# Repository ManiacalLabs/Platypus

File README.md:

# Platypus CNC / Laser Control Board

The Platypus is an Open Hardware CNC / Laser control board for running 2-axis GRBL with a wide variety of stepper motor driver options.

Unlike other Grbl boards that are just Arduino shields, the Platypus is a fully integrated solution with a built-in ATMega328p microcontroller and USB UART. 

Also, while other Grbl boards ignore it, the Platypus natively supports configuring Trinamic (TMC) StepStick drivers like the TMC2100 and TMC2208. Unlike normal StepStick motor drivers, the TMC variants use tri-state config pins which the Platypus provides.

# Specs

- Integrated ATMega328p Microcontroller (no arduino needed)
- CH340 USB to UART converter
- Screw terminals for all connections (plus male headers for motor and laser)
- Supports all standard StepStick-style motor drivers including TMC2100 and TMC2208
- Only 57mm x 75mm
- Robust USB-B connector

# Important Links

- [Usage](docs/Usage.md)
- [Assembly](docs/Assembly.md)

# Dimensions

# Contributing

This repository makes use of `git` submodules (primarily to handle KiCAD symbol and footprint libraries) and must be cloned with extra options.

Either clone the repo via:

```
git clone --recurse-submodules git@github.com:ManiacalLabs/Platypus.git
```

Or, if you already have the repo cloned or are using a fork:

```
git clone <EngravinatorRepo>
cd Engravinator
git submodule init
git submodule update
```

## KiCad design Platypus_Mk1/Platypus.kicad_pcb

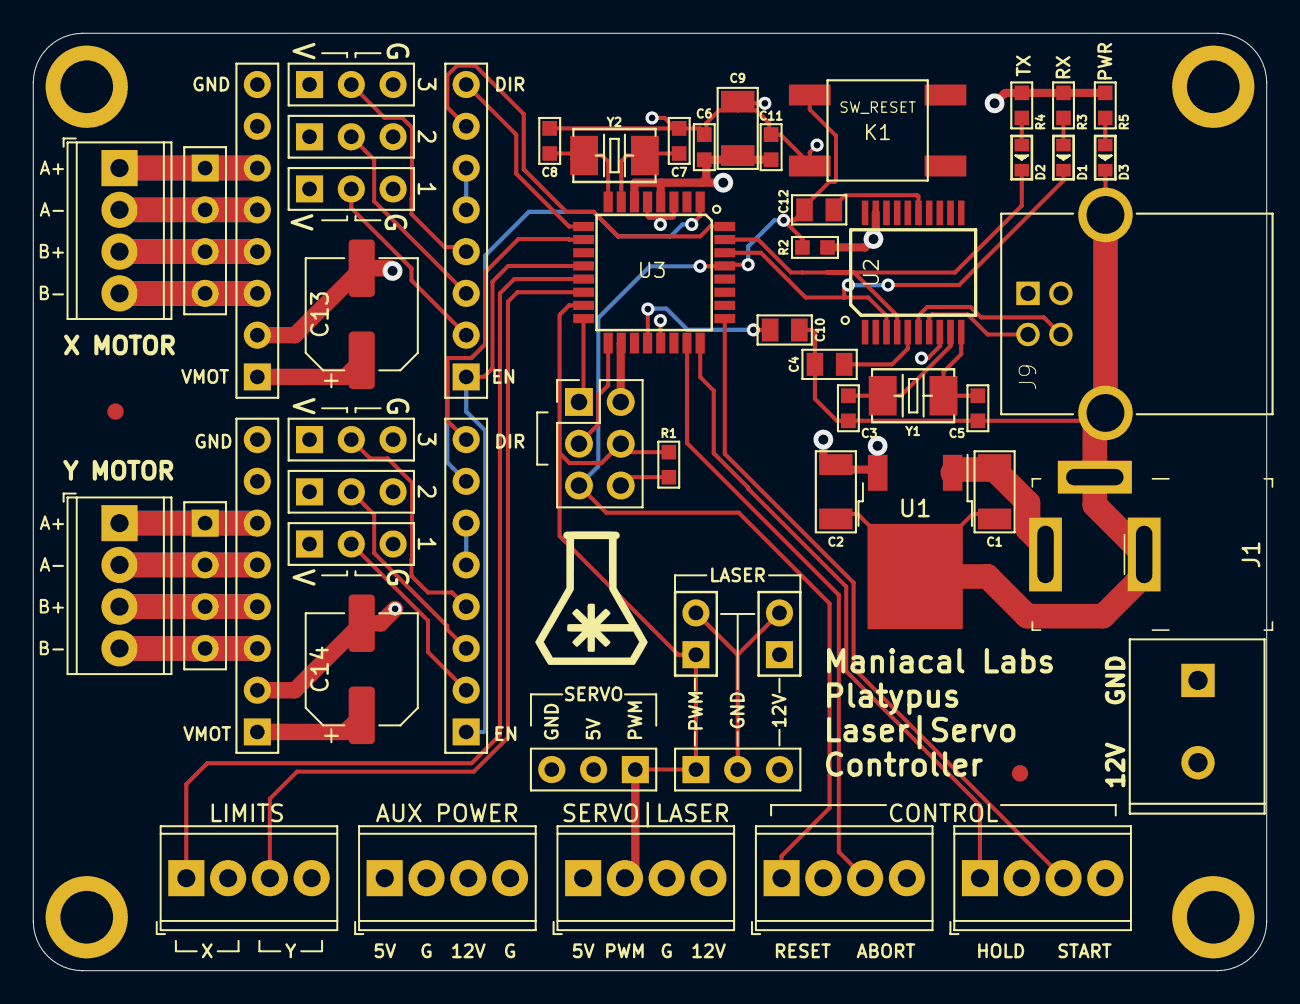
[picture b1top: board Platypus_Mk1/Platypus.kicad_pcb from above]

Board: 4 copper layers, 75.0 x 57.0 mm, 61 parts (0 on the bottom side), 47 nets.

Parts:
C1, C2, C9: 10uF; C1206
C3, C5, C7, C8: 22pF; C0603
C4, C10, C12: 100nF; C0805
C6, C11: 1uF; C0603
C13, C14: 47uF; CP_Elec_6.3x5.4
CN1: SERVO_PWM; H3-2.54
CN2, CN3, CN4, CN7, CN8, CN9: CFG1; H3-2.54
CN5, CN10: FEMALE_LEFT; H8-2.54
CN6, CN11: FEMALE_RIGHT; H8-2.54
CN12: LASER_CONN; H3-2.54
D1, D2, D3: LED_RED; LED-0603
FID1, FID2: Fiducial; Fiducial_1mm_Dia_2mm_Outer
H1, H2, H3, H4: Mount; MountingHole_2.5mm_Pad
J1: PJ-202AH; Barrel_Jack_5.5mmODx2.1mmID_PJ-202A
J2: TermLaser; TerminalBlock_Phoenix_MPT-0,5-4-2.54_1x04_P2.54mm_Horizontal
J3: TermStop; TerminalBlock_Phoenix_MPT-0,5-4-2.54_1x04_P2.54mm_Horizontal
J4: LASER_PWR; H2-2.54
J5: LASER_PULSE; H2-2.54
J6: TermControl; TerminalBlock_Phoenix_MPT-0,5-4-2.54_1x04_P2.54mm_Horizontal
J7: TermLimit; TerminalBlock_Phoenix_MPT-0,5-4-2.54_1x04_P2.54mm_Horizontal
J8: TermAux; TerminalBlock_Phoenix_MPT-0,5-4-2.54_1x04_P2.54mm_Horizontal
J9: UJ2-BH-1-TH; CUI_UJ2-BH-1-TH
J10: ICSP; PinHeader_2x03_P2.54mm_Vertical
J11, J13: MotorTerm; TerminalBlock_Phoenix_MPT-0,5-4-2.54_1x04_P2.54mm_Horizontal
J12, J14: MotorHeader; H4-2.54
J15: 12V_TERM; H2-5.0-10.5X8.0MM
K1: SW_RESET; SW4-SMD-6.0X6.0X5.0MM
R1, R2: 10K; R0603
R3, R4, R5: 1K; R0603
U1: CJ7805; TO-252-2
U2: INTERFACE-CH340T_SSOP20_; SSOP20-0.65-7.6X5.2MM
U3: MCU-ATMEGA328P-AU_TQFP32_; TQFP32-0.8-7X7MM
Y1: 12MHz; X2-SMD-5.0X3.2X1.3MM
Y2: 16MHZ; X2-SMD-5.0X3.2X1.3MM

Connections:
5V: C2.1, C6.2, C9.1, C11.2, CN1.2, CN2.1, CN3.1, CN4.1, CN6.7, CN7.1, CN8.1, CN9.1, CN11.7, J2.1, J8.1, J10.2, R2.2, R3.2, R4.1, R5.2, U1.3, U2.19, U3.4, U3.6, U3.18
/Arduino Nano/D12: J10.1, U3.16
/Arduino Nano/D13: J10.3, U3.17
/GRBL_ABORT: J3.3, U3.23
/GRBL_RX: D1.2, U2.3, U3.30
/GRBL_TX: D2.2, U2.4, U3.31
/HOLD: J6.1, U3.24
/NANO_RESET: C12.1, J3.1, J10.5, K1.3, R2.1, U3.29
/PULSE: CN1.1, CN12.1, J2.2, J5.1, J10.4, R1.2, U3.15
/START: J6.3, U3.25
/STEP_EN: CN5.1, CN10.1, U3.12
/StepDriverX/CFG1: CN2.2, CN5.2
/StepDriverX/CFG2: CN3.2, CN5.3
/StepDriverX/CFG3: CN4.2, CN5.4
/StepDriverY/CFG1: CN7.2, CN10.2
/StepDriverY/CFG2: CN8.2, CN10.3
/StepDriverY/CFG3: CN9.2, CN10.4
/VIN_12V: C1.1, C13.1, C14.1, CN6.1, CN11.1, CN12.3, J1.1, J2.4, J4.1, J8.3, J15.2, U1.1
/X_DIR: CN5.8, U3.9
/X_LIMIT: J7.1, U3.13
/X_STEP: CN5.7, U3.32
/Y_DIR: CN10.8, U3.10
/Y_LIMIT: J7.3, U3.14
/Y_STEP: CN10.7, U3.1
GND: C1.2, C2.2, C3.1, C4.2, C5.1, C6.1, C7.2, C8.1, C9.2, C10.2, C11.1, C13.2, C14.2, CN1.3, CN2.3, CN3.3, CN4.3, CN6.2, CN6.8, CN7.3, CN8.3, CN9.3, CN11.2, CN11.8, CN12.2, D3.2, H1.1, H2.1, H3.1, H4.1, J1.2, J1.3, J2.3, J3.2, J3.4, J4.2, J5.2, J6.2, J6.4, J7.2, J7.4, J8.2, J8.4, J9.4, J9.SH1, J9.SH2, J10.6, J15.1, K1.4, R1.1, U1.2, U2.8, U3.3, U3.5, U3.21
unnamed: C3.2, U2.9, Y1.2
unnamed: C4.1, U2.5
unnamed: C5.2, U2.10, Y1.1
unnamed: C7.1, U3.7, Y2.1
unnamed: C8.2, U3.8, Y2.2
unnamed: C10.1, U3.20
unnamed: C12.2, U2.15
unnamed: CN5.5, CN5.6
unnamed: CN6.3, J11.4, J12.4
unnamed: CN6.4, J11.3, J12.3
unnamed: CN6.5, J11.2, J12.2
unnamed: CN6.6, J11.1, J12.1
unnamed: CN10.5, CN10.6
unnamed: CN11.3, J13.4, J14.4
unnamed: CN11.4, J13.3, J14.3
unnamed: CN11.5, J13.2, J14.2
unnamed: CN11.6, J13.1, J14.1
unnamed: D1.1, R3.1
unnamed: D2.1, R4.2
unnamed: D3.1, R5.1
unnamed: J9.2, U2.7
unnamed: J9.3, U2.6

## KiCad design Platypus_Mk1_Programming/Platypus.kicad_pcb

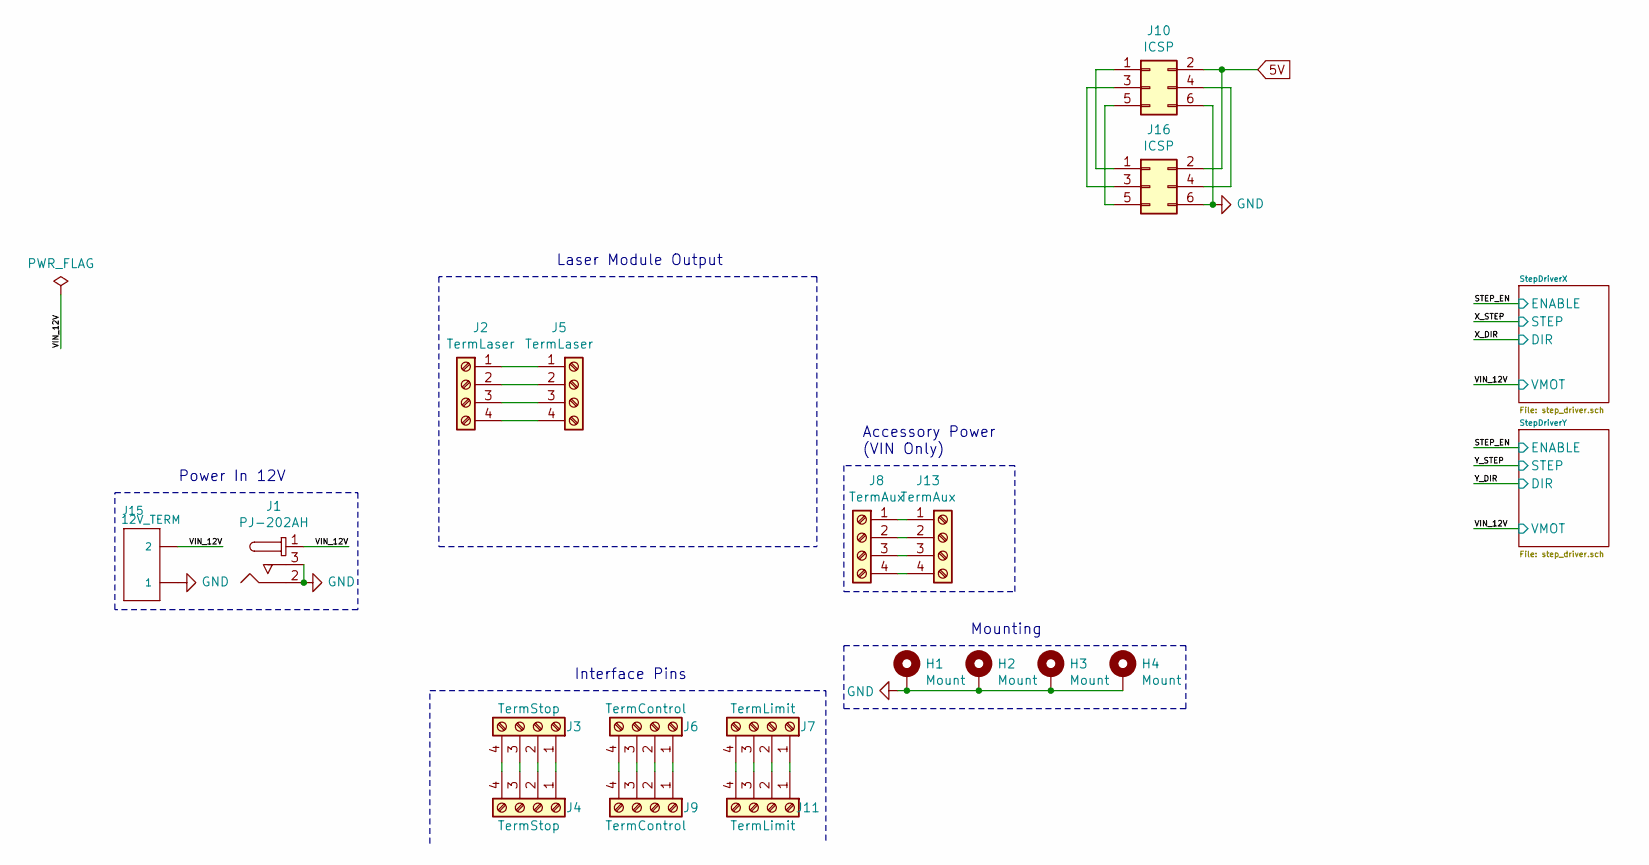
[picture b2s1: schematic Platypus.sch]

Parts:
H1, H2, H3, H4: Mount; MountingHole_2.5mm_Pad
J1: PJ-202AH; Barrel_Jack_5.5mmODx2.1mmID_PJ-202A; MPN PJ-202AH; Digi-Key_PN CP-202AH-ND
J2, J5: TermLaser; TerminalBlock_Phoenix_MPT-0,5-4-2.54_1x04_P2.54mm_Horizontal; MPN GS019-2.54-04P-5
J3, J4: TermStop; TerminalBlock_Phoenix_MPT-0,5-4-2.54_1x04_P2.54mm_Horizontal; MPN GS019-2.54-04P-5
J6, J9: TermControl; TerminalBlock_Phoenix_MPT-0,5-4-2.54_1x04_P2.54mm_Horizontal; MPN GS019-2.54-04P-5
J7, J11: TermLimit; TerminalBlock_Phoenix_MPT-0,5-4-2.54_1x04_P2.54mm_Horizontal; MPN GS019-2.54-04P-5
J8, J13: TermAux; TerminalBlock_Phoenix_MPT-0,5-4-2.54_1x04_P2.54mm_Horizontal; MPN GS019-2.54-04P-5
J10, J16: ICSP; PinHeader_2x03_P2.54mm_Vertical; MPN P125-12A1BS116A1
J15: 12V_TERM; H2-5.0-10.5X8.0MM

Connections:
5V: J10.2, J16.2; also elsewhere on the board
/VIN_12V: J1.1, J15.2; also elsewhere on the board
GND: H1.1, H2.1, H3.1, H4.1, J1.2, J1.3, J10.6, J15.1, J16.6; also elsewhere on the board
unnamed: J2.1, J5.1
unnamed: J2.2, J5.2
unnamed: J2.3, J5.3
unnamed: J2.4, J5.4
unnamed: J3.1, J4.1
unnamed: J3.2, J4.2
unnamed: J3.3, J4.3
unnamed: J3.4, J4.4
unnamed: J6.1, J9.1
unnamed: J6.2, J9.2
unnamed: J6.3, J9.3
unnamed: J6.4, J9.4
unnamed: J10.1, J16.1
unnamed: J10.3, J16.3
unnamed: J10.4, J16.4
unnamed: J10.5, J16.5
unnamed: J7.1, J11.1
unnamed: J7.2, J11.2
unnamed: J7.3, J11.3
unnamed: J7.4, J11.4
unnamed: J8.1, J13.1
unnamed: J8.2, J13.2
unnamed: J8.3, J13.3
unnamed: J8.4, J13.4

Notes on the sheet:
Accessory Power (VIN Only)
Laser Module Output
Interface Pins
Power In 12V
Mounting

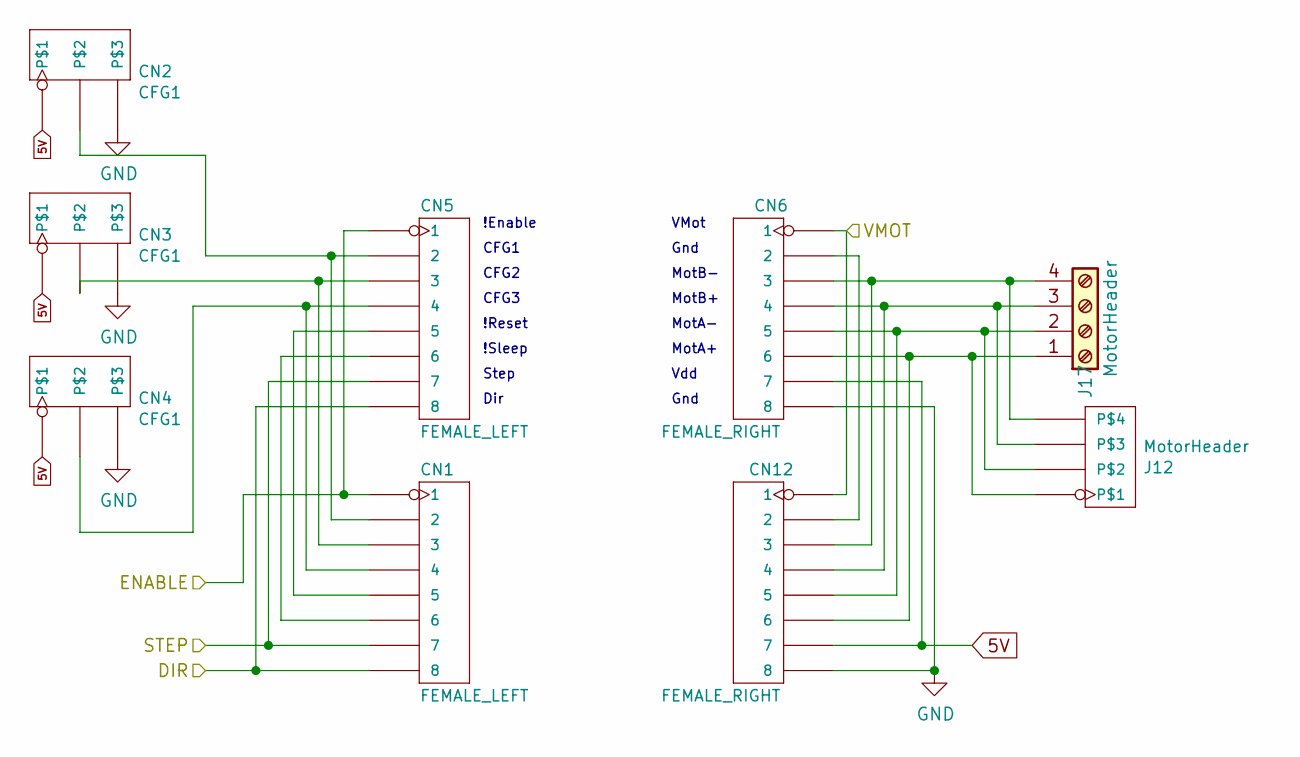
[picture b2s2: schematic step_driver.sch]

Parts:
CN1, CN5: FEMALE_LEFT; H8-2.54; MPN F185-1108A1BSYC1
CN2, CN3, CN4: CFG1; H3-2.54
CN6, CN12: FEMALE_RIGHT; H8-2.54; MPN F185-1108A1BSYC1
J12: MotorHeader; H4-2.54; MPN P125-1104A0BS116A1
J17: MotorHeader; TerminalBlock_Phoenix_MPT-0,5-4-2.54_1x04_P2.54mm_Horizontal; MPN GS019-2.54-04P-5

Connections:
5V: CN2.1, CN3.1, CN4.1, CN6.7, CN12.7; also elsewhere on the board
/STEP_EN: CN1.1, CN5.1; also elsewhere on the board
/VIN_12V: CN6.1, CN12.1; also elsewhere on the board
/X_DIR: CN1.8, CN5.8
/X_STEP: CN1.7, CN5.7
GND: CN2.3, CN3.3, CN4.3, CN6.8, CN12.8; also elsewhere on the board
unnamed: CN1.2, CN2.2, CN5.2
unnamed: CN1.3, CN3.2, CN5.3
unnamed: CN1.4, CN4.2, CN5.4
unnamed: CN1.5, CN5.5
unnamed: CN1.6, CN5.6
unnamed: CN6.2, CN12.2
unnamed: CN6.3, CN12.3, J12.4, J17.4
unnamed: CN6.4, CN12.4, J12.3, J17.3
unnamed: CN6.5, CN12.5, J12.2, J17.2
unnamed: CN6.6, CN12.6, J12.1, J17.1

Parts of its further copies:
CN7, CN8, CN9: CFG1; H3-2.54
CN10, CN13: FEMALE_LEFT; H8-2.54; MPN F185-1108A1BSYC1
CN11, CN14: FEMALE_RIGHT; H8-2.54; MPN F185-1108A1BSYC1
J14: MotorHeader; H4-2.54; MPN P125-1104A0BS116A1
J18: MotorHeader; TerminalBlock_Phoenix_MPT-0,5-4-2.54_1x04_P2.54mm_Horizontal; MPN GS019-2.54-04P-5

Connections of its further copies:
5V: CN7.1, CN8.1, CN9.1, CN11.7, CN14.7; also elsewhere on the board
/STEP_EN: CN10.1, CN13.1; also elsewhere on the board
/VIN_12V: CN11.1, CN14.1; also elsewhere on the board
/Y_DIR: CN10.8, CN13.8
/Y_STEP: CN10.7, CN13.7
GND: CN7.3, CN8.3, CN9.3, CN11.8, CN14.8; also elsewhere on the board
unnamed: CN7.2, CN10.2, CN13.2
unnamed: CN8.2, CN10.3, CN13.3
unnamed: CN9.2, CN10.4, CN13.4
unnamed: CN10.5, CN13.5
unnamed: CN10.6, CN13.6
unnamed: CN11.2, CN14.2
unnamed: CN11.3, CN14.3, J14.4, J18.4
unnamed: CN11.4, CN14.4, J14.3, J18.3
unnamed: CN11.5, CN14.5, J14.2, J18.2
unnamed: CN11.6, CN14.6, J14.1, J18.1

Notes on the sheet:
!Enable
CFG1
CFG2
CFG3
!Reset
!Sleep
Step
Dir
VMot
Gnd
MotB-
MotB+
MotA-
MotA+
Vdd

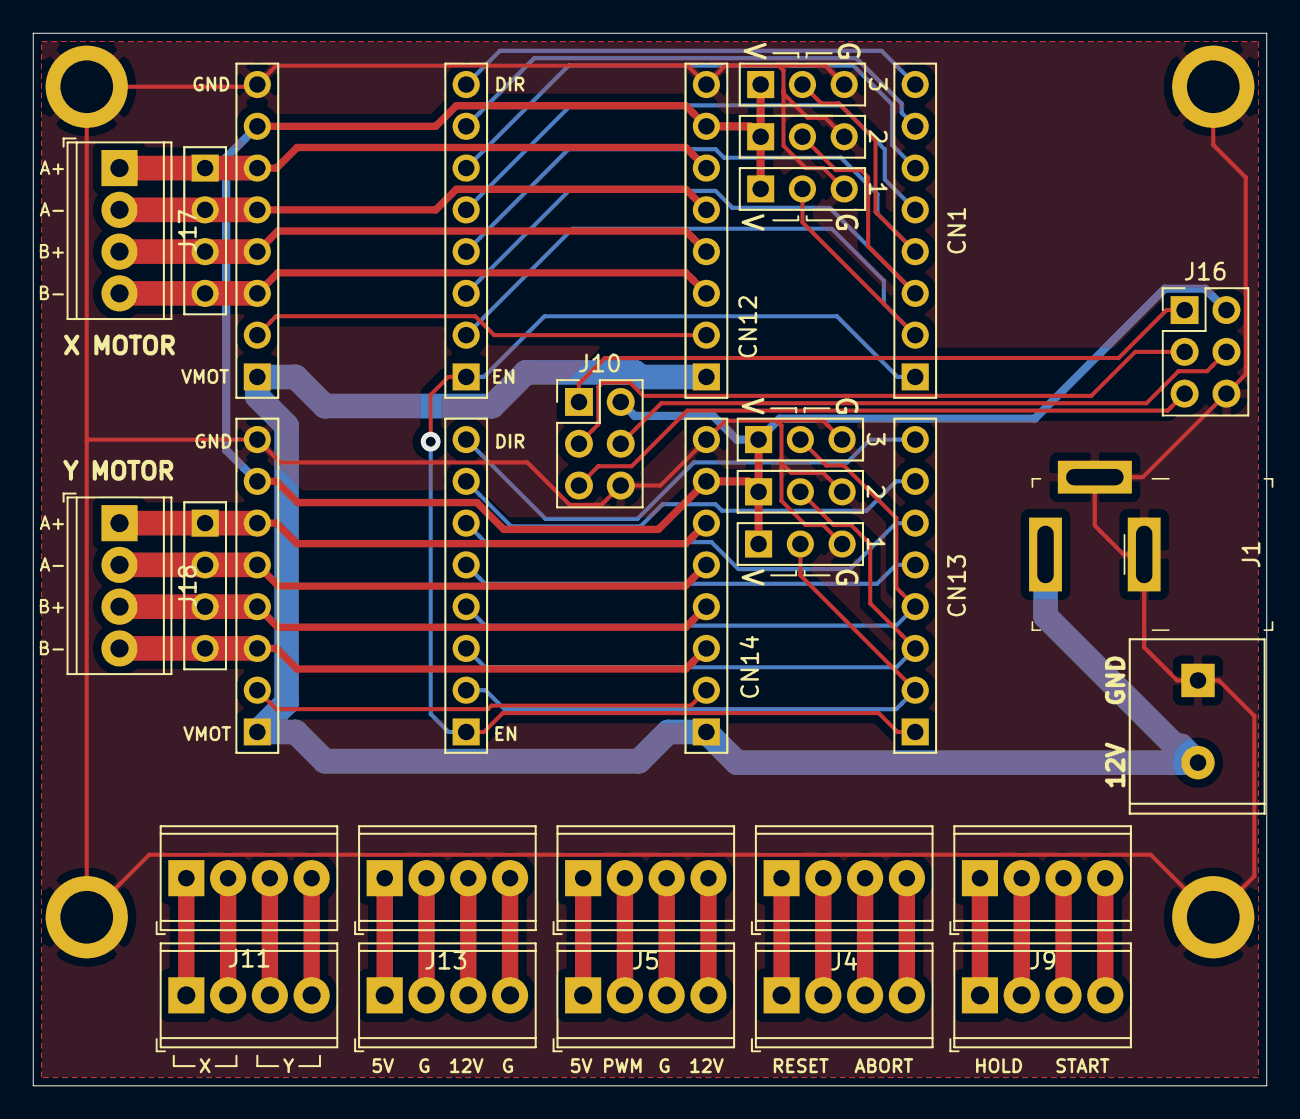
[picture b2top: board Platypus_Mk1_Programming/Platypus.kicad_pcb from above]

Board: 2 copper layers, 75.0 x 64.0 mm, 36 parts (0 on the bottom side), 52 nets.

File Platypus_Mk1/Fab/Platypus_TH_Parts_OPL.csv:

Part/Designator,Manufacture Part Number/Seeed SKU,Quantity
"J4,J5",320020016,2
"J12,J14",320020017,2
J10,320020077,1
"CN1,CN2,CN3,CN4,CN7,CN8,CN9,CN12",320020079,8
"CN5,CN6,CN10,CN11",320030061,4
J15,320110031,1
"J2,J3,J6,J7,J8,J11,J13",320110118 - GS019 4 pin screw terminal ,7

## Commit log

2019-08-06 initial setup
2019-08-06 Added Arduino Nano component
2019-08-06 Add nano to main sheet
2019-08-06 Starting on step driver module
2019-08-07 Minor update to stepper
2019-08-07 Almost complete schematic
2019-08-07 adding digikey libs
2019-08-07 Complete schematic
2019-08-07 Set more footprints
2019-08-07 Add IC footprints
2019-08-08 Creating Pi layout
2019-08-08 Probably giving up on Pi option
2019-08-09 More power routing
2019-08-09 power and nano cleanup
2019-08-09 temp remove submodules
2019-08-09 Add back submodules
2019-08-09 Added license and readme
2019-08-10 Mostly final layout
2019-08-10 Near complete layout
2019-08-10 Beta v1
2019-08-10 Starting to add 3D models
2019-08-10 Finished adding 3D models
2019-08-10 Fixing 10uF caps
2019-08-10 fix 2 missing cap models
2019-08-14 Add fab files
2019-08-29 Moving into own repo
2019-08-29 Update submodules
2019-08-29 Trying to fix submodules
2019-08-29 Readd submodules correctly
2019-08-29 Look, submodule is hard
2019-08-29 Fix README
2019-08-30 Increase mount hole size
2019-09-09 Change RX/TX LEDs. Add new laser conn
2019-09-09 rework for component moves
2019-09-10 Adding platypus graphic
2019-09-11 Update fab files
2019-09-11 Addinge license note to board back
2019-09-11 Adding stepper driver labels
2019-10-09 Adding step file and solder jig
2019-10-11 remove boarder from gerbers
2019-10-17 Add programming board
2019-11-05 Fixing programmer hole sizes
2019-11-10 Adding usage doc
2019-11-10 Add LightBurn setup
2019-11-11 add laserweb doc
2019-11-11 Added driver section
2019-11-11 Added specs
2019-11-19 Adding updated step file
2019-11-19 Add flash and test utils
2019-11-21 update base flash tools
2019-11-23 Adding movement checks
2019-12-15 Adding assembly guide
2019-12-15 Add assembly link
2019-12-15 Adding dimensions doc
2019-12-16 tweak description
2019-12-16 tweak assembly guide
2019-12-16 Add doc license

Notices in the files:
Platypus_Mk1/Platypus.kicad_pcb:
Licensed Under CERN OHL v1.2
